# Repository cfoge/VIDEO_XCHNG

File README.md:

# VIDEO_XCHNG

It's an experimental video tool for VJs and experimental video artists that I think you are really going to dig. Think of it as a swiss army knife for joining all your old video gear together. 

  The "Video XCHNG" (Video Exchange) was created to expand the possibilities of working with analogue video gear by adding a number of features that will greatly improve the way you work with your vintage equipment.

                       These features include:
                       - Two x 2:1 switches, add two additional inputs to your video mixer
                       - A dirty mixer for creating distortion and disruption as your transition between two video inputs
                       - A passive sharpener to heighten the edges of your signal (a classic effect)
                       - A loop out/bypass function to switch from direct feedback to feedback with effects instantly
                       
MANUAL: https://docs.google.com/document/d/13PXkH_QpwMR1RbXq8WSNVv7c3W7H49q0wkpC9X-2hgI/edit?usp=sharing

BUILD GUIDE: https://docs.google.com/document/d/1K-kYqIZa-mxv5eNUbX9vSpcRY2loV5x1ImC7kZpjctI/edit?usp=sharing

BOM: https://docs.google.com/spreadsheets/d/1kL9SzumbGBxzcogHdAwO_ZjvOIKyRkfr3qArjTiD70w/edit?usp=sharing

LINK TO THE KICKSTARTER: https://www.kickstarter.com/projects/synth-bt/video-xchng-expand-your-experimental-video-rig/description

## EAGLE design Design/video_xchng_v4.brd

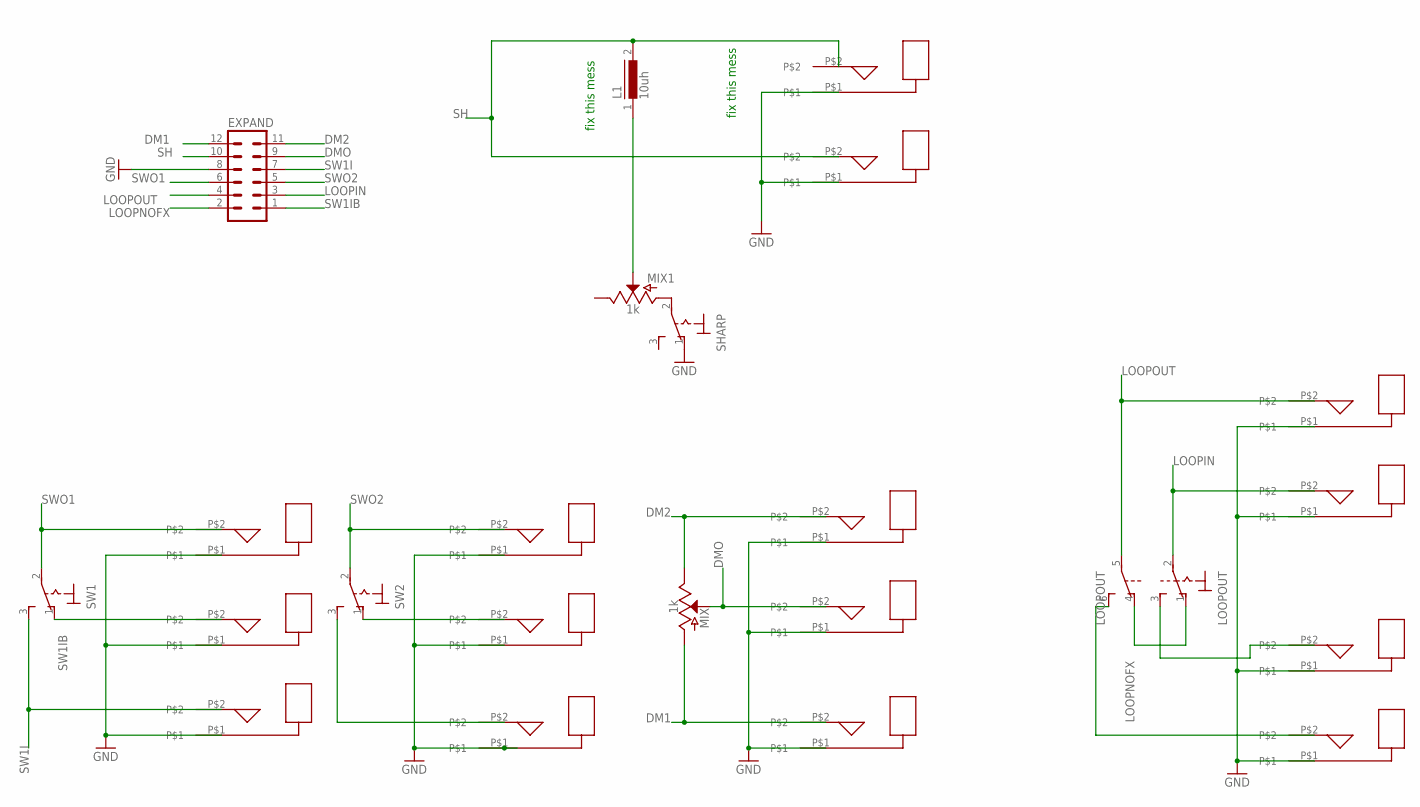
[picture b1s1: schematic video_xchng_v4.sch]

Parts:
EXPAND: MA06-2
L1: 10uh; LBC15
LOOPOUT: M9040P2
MIX, MIX1: 1k; POT-PTH-ALPS
SHARP: M9040P
SHARPIN: RCJJACK,VERTICAL,PCBMOUNT
SW1, SW2: M9040P
U$1, U$2, U$3, U$4, U$5, U$6, U$7, U$8, U$9, U$10, U$11, U$12, U$13, U$15: RCJJACK,VERTICAL,PCBMOUNT

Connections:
DM1: EXPAND.12, MIX.P$3 (A), U$9.P$2
DM2: EXPAND.11, MIX.P$1 (E), U$7.P$2
DMO: EXPAND.9, MIX.P$2 (S), U$8.P$2
GND: EXPAND.8, SHARP.1 (O), SHARPIN.P$1, U$1.P$1, U$2.P$1, U$3.P$1, U$4.P$1, U$5.P$1, U$6.P$1, U$7.P$1, U$8.P$1, U$9.P$1, U$10.P$1, U$11.P$1, U$12.P$1, U$13.P$1, U$15.P$1
LOOPIN: EXPAND.3, LOOPOUT.2, U$11.P$2
LOOPNOFX: EXPAND.2, LOOPOUT.1 (O), LOOPOUT.4 (O)
LOOPOUT: EXPAND.4, LOOPOUT.5, U$10.P$2
unnamed: MIX1.P$3 (A), SHARP.2
unnamed: SW2.1 (O), U$5.P$2
unnamed: SW2.3 (S), U$6.P$2
unnamed: LOOPOUT.3 (S), U$12.P$2
unnamed: LOOPOUT.6 (S), U$13.P$2
unnamed: L1.1, MIX1.P$2 (S)
SH: EXPAND.10, L1.2, SHARPIN.P$2, U$15.P$2
SW1I: EXPAND.7, SW1.3 (S), U$3.P$2
SW1IB: EXPAND.1, SW1.1 (O), U$2.P$2
SWO1: EXPAND.6, SW1.2, U$1.P$2
SWO2: EXPAND.5, SW2.2, U$4.P$2

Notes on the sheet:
fix this mess

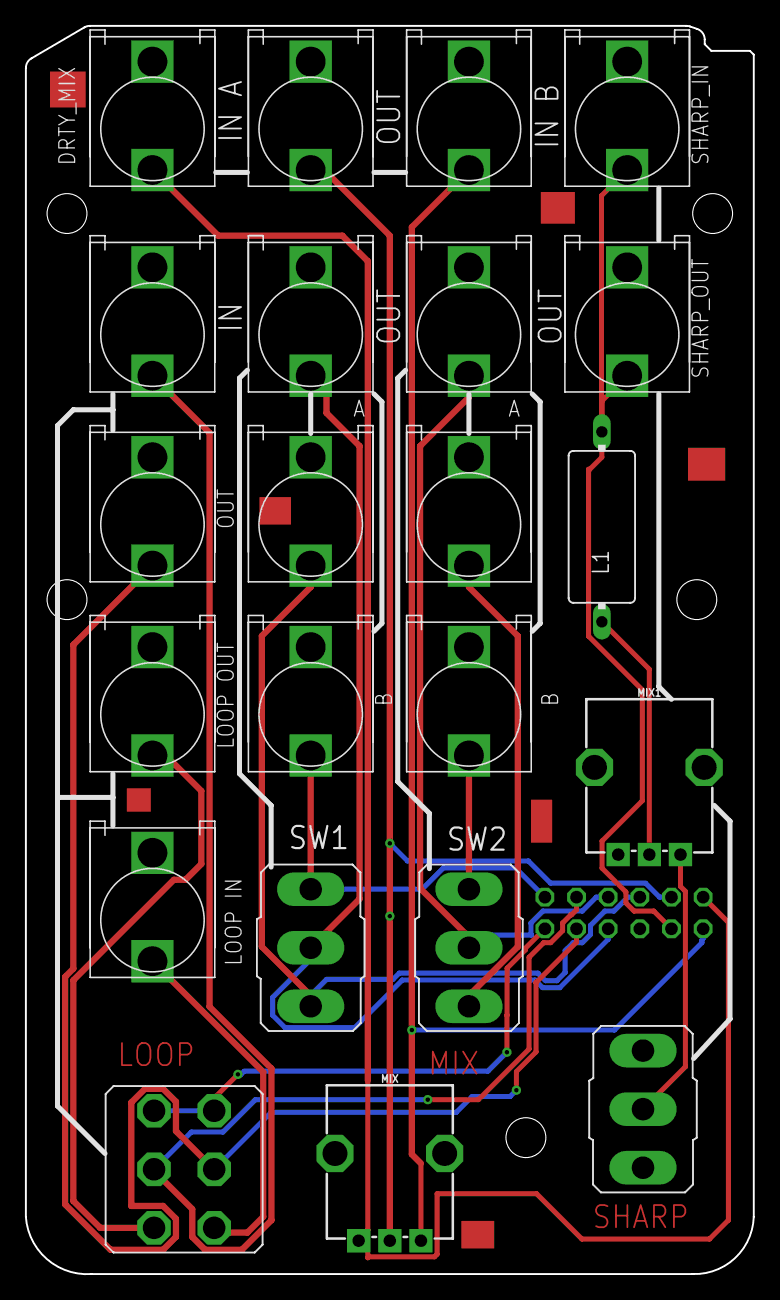
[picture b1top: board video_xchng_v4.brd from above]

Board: 2 copper layers, 58.4 x 100.2 mm, 23 parts (1 on the bottom side), 18 nets.

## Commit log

2021-06-16 Add files via upload
    blank cheat sheets added
2021-08-08 added design files
2021-08-08 Add files via upload
    Front panels added

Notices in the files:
parts and their libraries:
SparkFun-Resistors: Licensing: Creative Commons ShareAlike 4.0 International - https://creativecommons.org/licenses/by-sa/4.0
